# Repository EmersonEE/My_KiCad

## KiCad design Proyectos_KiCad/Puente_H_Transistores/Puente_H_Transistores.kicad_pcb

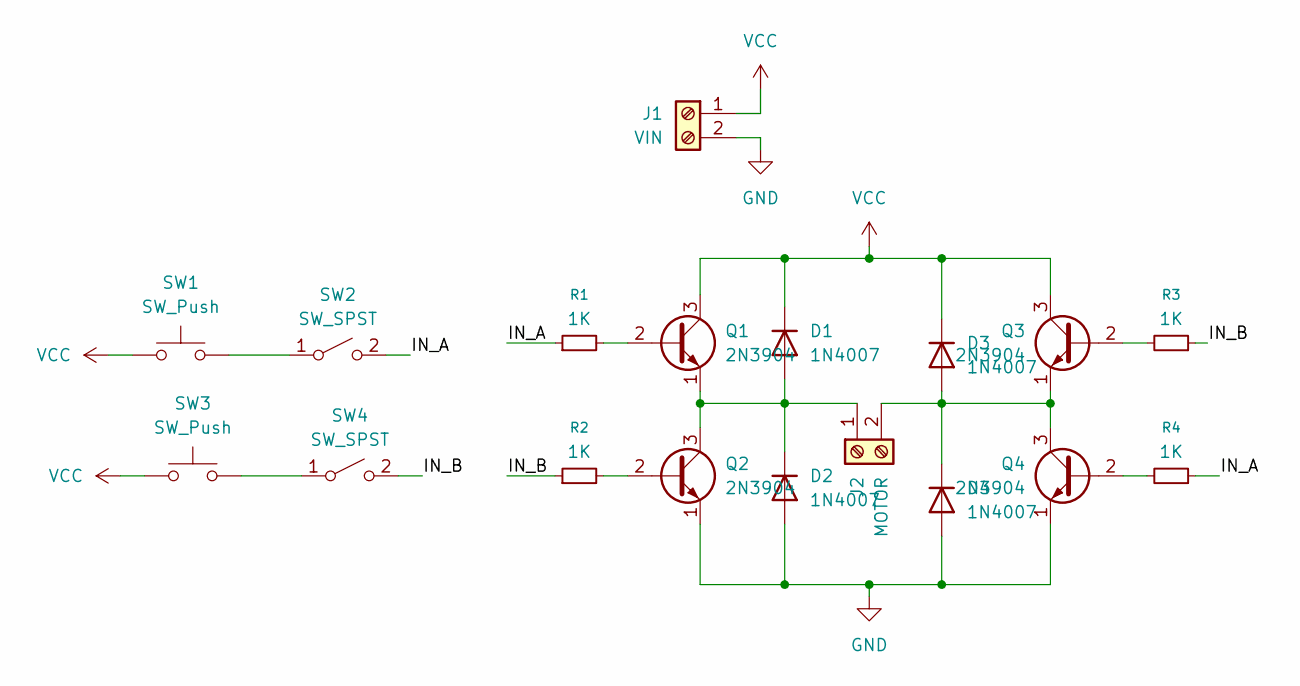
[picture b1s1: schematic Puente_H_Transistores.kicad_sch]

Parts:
D1, D2, D3, D4: 1N4007; D_DO-41_SOD81_P10.16mm_Horizontal
J1: VIN; TerminalBlock_Phoenix_MKDS-1,5-2-5.08_1x02_P5.08mm_Horizont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
J2: MOTOR; TerminalBlock_Phoenix_MKDS-1,5-2-5.08_1x02_P5.08mm_Horizont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
Q1, Q2, Q3, Q4: 2N3904; TO-92L_Inline_Wide
R1, R2, R3, R4: 1K; R_Axial_DIN0207_L6.3mm_D2.5mm_P10.16mm_Horizontal
SW1, SW3: SW_Push; TerminalBlock_Phoenix_MKDS-1,5-2-5.08_1x02_P5.08mm_Horizont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
SW2, SW4: SW_SPST; TerminalBlock_Phoenix_MKDS-1,5-2-5.08_1x02_P5.08mm_Horizont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

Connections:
/IN_A: R1.1, R4.1, SW2.2 (B)
/IN_B: R2.1, R3.1, SW4.2 (B)
GND: D2.2 (A), D4.2 (A), J1.2, Q2.1 (E), Q4.1 (E)
unnamed: D1.2 (A), D2.1 (K), J2.1, Q1.1 (E), Q2.3 (C)
unnamed: D3.2 (A), D4.1 (K), J2.2, Q3.1 (E), Q4.3 (C)
unnamed: Q1.2 (B), R1.2
unnamed: Q2.2 (B), R2.2
unnamed: Q3.2 (B), R3.2
unnamed: Q4.2 (B), R4.2
unnamed: SW1.2, SW2.1 (A)
unnamed: SW3.2, SW4.1 (A)
VCC: D1.1 (K), D3.1 (K), J1.1, Q1.3 (C), Q3.3 (C), SW1.1, SW3.1

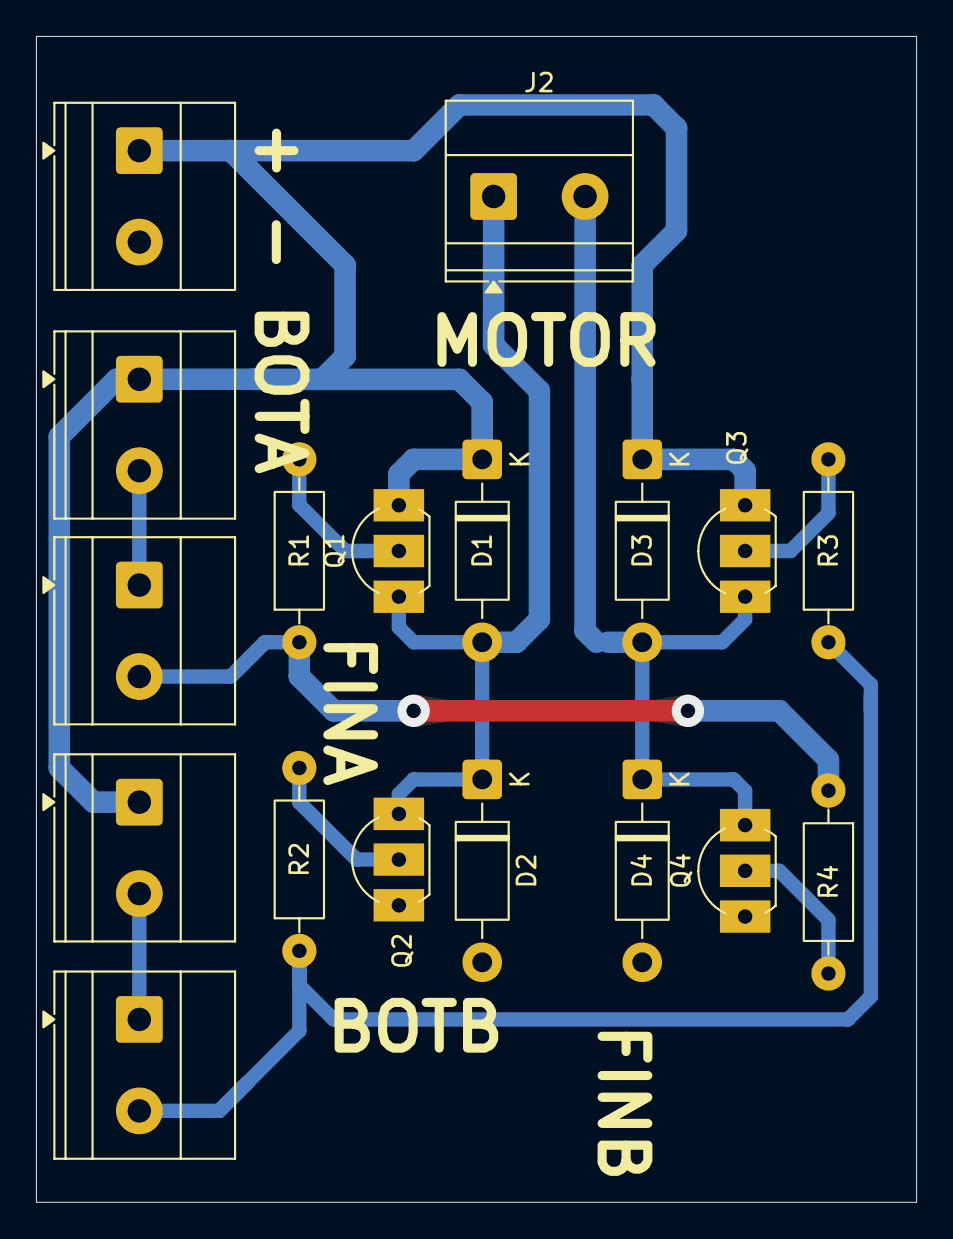
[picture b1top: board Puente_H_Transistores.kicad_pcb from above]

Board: 2 copper layers, 48.9 x 64.8 mm, 18 parts (0 on the bottom side), 12 nets.

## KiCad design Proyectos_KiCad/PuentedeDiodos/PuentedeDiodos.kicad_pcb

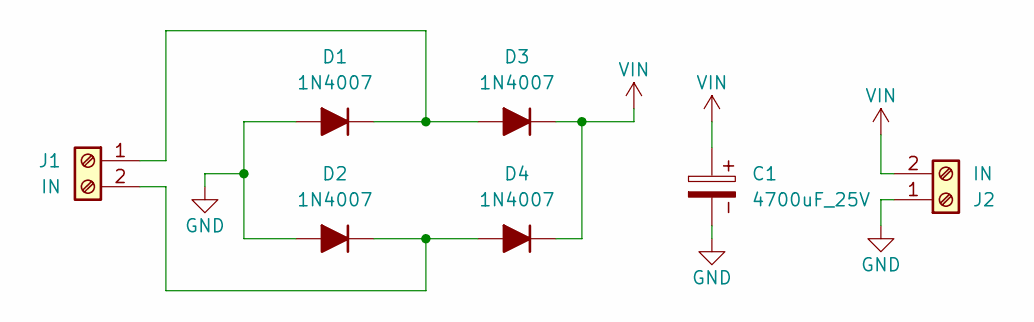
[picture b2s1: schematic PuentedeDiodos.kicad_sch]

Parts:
C1: 4700uF_25V; CP_Radial_D18.0mm_P7.50mm
D1, D2, D3, D4: 1N4007; D_DO-41_SOD81_P7.62mm_Horizontal
J1, J2: IN; TerminalBlock_Phoenix_MKDS-1,5-2-5.08_1x02_P5.08mm_Horizont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

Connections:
GND: C1.2, D1.2 (A), D2.2 (A), J2.1
unnamed: D1.1 (K), D3.2 (A), J1.1
unnamed: D2.1 (K), D4.2 (A), J1.2
VIN: C1.1, D3.1 (K), D4.1 (K), J2.2

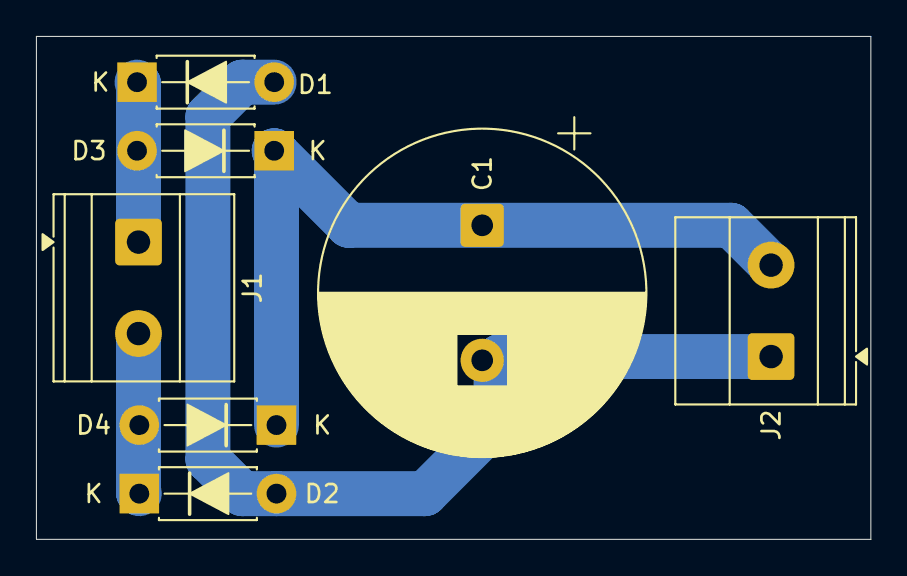
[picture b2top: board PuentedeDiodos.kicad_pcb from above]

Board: 2 copper layers, 46.4 x 27.9 mm, 7 parts (0 on the bottom side), 4 nets.

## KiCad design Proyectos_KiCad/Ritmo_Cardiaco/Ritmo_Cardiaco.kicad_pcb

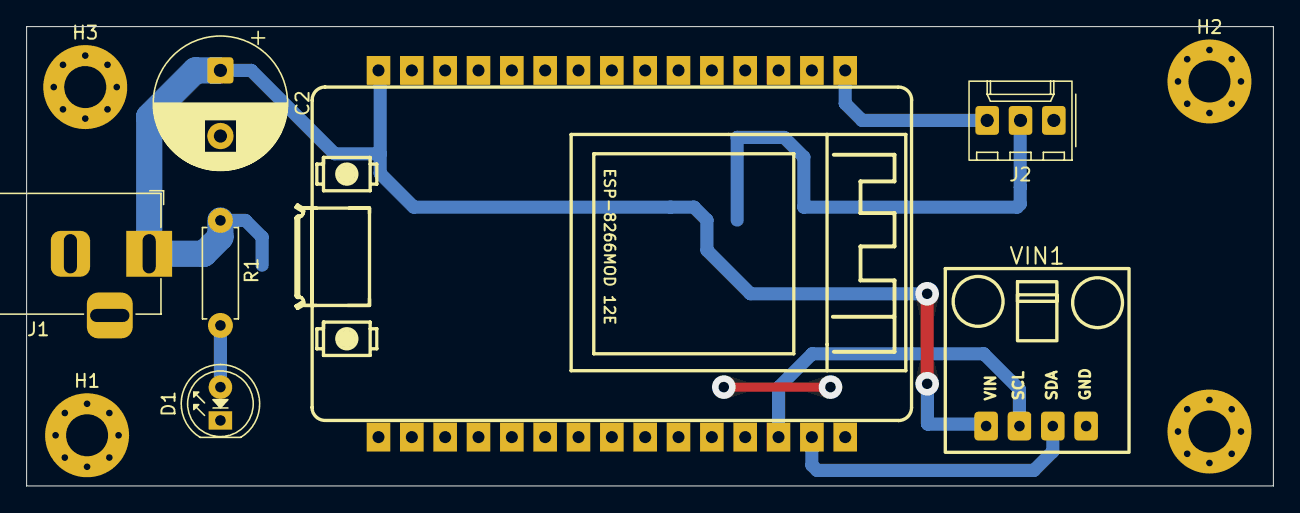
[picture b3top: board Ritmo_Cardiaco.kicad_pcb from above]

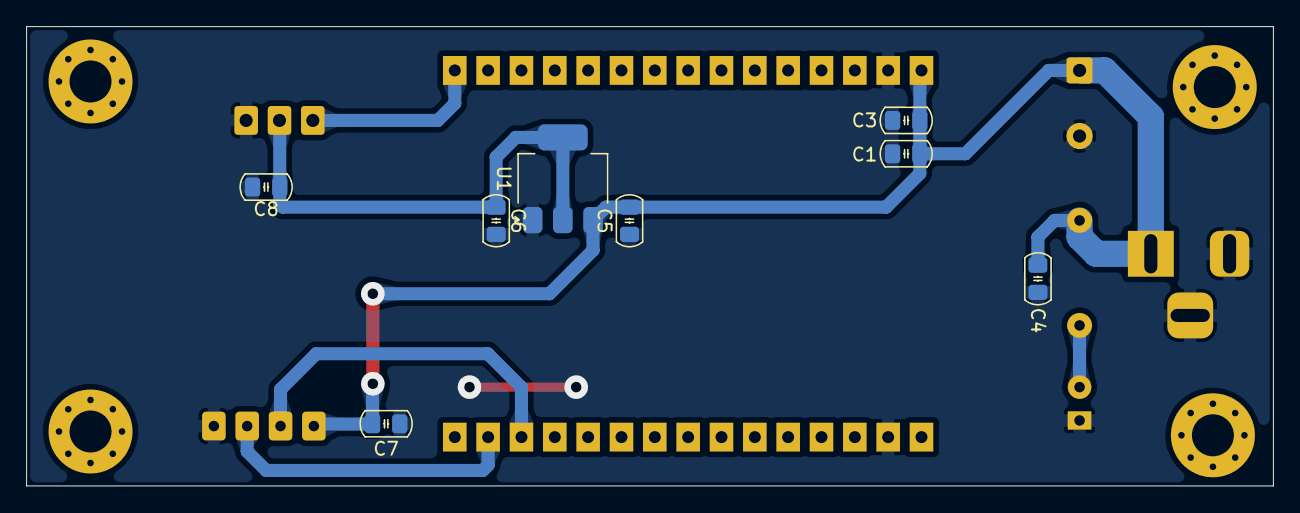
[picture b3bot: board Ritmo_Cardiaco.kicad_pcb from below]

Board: 2 copper layers, 95.0 x 35.0 mm, 19 parts (8 on the bottom side), 7 nets.

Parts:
C1, C3, C4, C7, C8: 100nF; C_0805_2012Metric_Pad1.18x1.45mm
C2: 250uF/15V; CP_Radial_D10.0mm_P5.00mm
C5, C6: 10uF/16V; C_0805_2012Metric_Pad1.18x1.45mm
D1: RED; LED_D5.0mm
H1, H2, H3, H4: MountingHole_3.2mm_M3_Pad_Via
J1: Barrel_Jack_Switch; BarrelJack_Horizontal
J2: SENSOR; Molex_KK-254_AE-6410-03A_1x03_P2.54mm_Vertical
NODE1: MCU-ESP8266; NODEMCU-12E_Grande
R1: 2K
U1: AMS1117-3.3; SOT-223-3_TabPin2
VIN1: MAX30102; MAX30102-MODULE-FOOTPRINT

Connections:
+3.3V: C6.1, C8.1, J2.2, U1.2 (VO)
+5V: C1.1, C2.1, C3.1, C4.1, C5.1, C7.1, J1.1, NODE1.29 (Vin), R1.1, U1.3 (VI), VIN1.1 (VIN)
GND: C1.2, C2.2, C3.2, C4.2, C5.2, C6.2, C7.2, C8.2, D1.1 (K), J1.2, J1.3, J2.1, NODE1.13 (GND), NODE1.28 (GND), U1.1 (GND), VIN1.4 (GND)
unnamed: D1.2 (A), R1.2
SCL: NODE1.2 (D2), VIN1.2 (SCL)
SDA: NODE1.1 (D1), VIN1.3 (SDA)
SEN: J2.3, NODE1.15 (A0)

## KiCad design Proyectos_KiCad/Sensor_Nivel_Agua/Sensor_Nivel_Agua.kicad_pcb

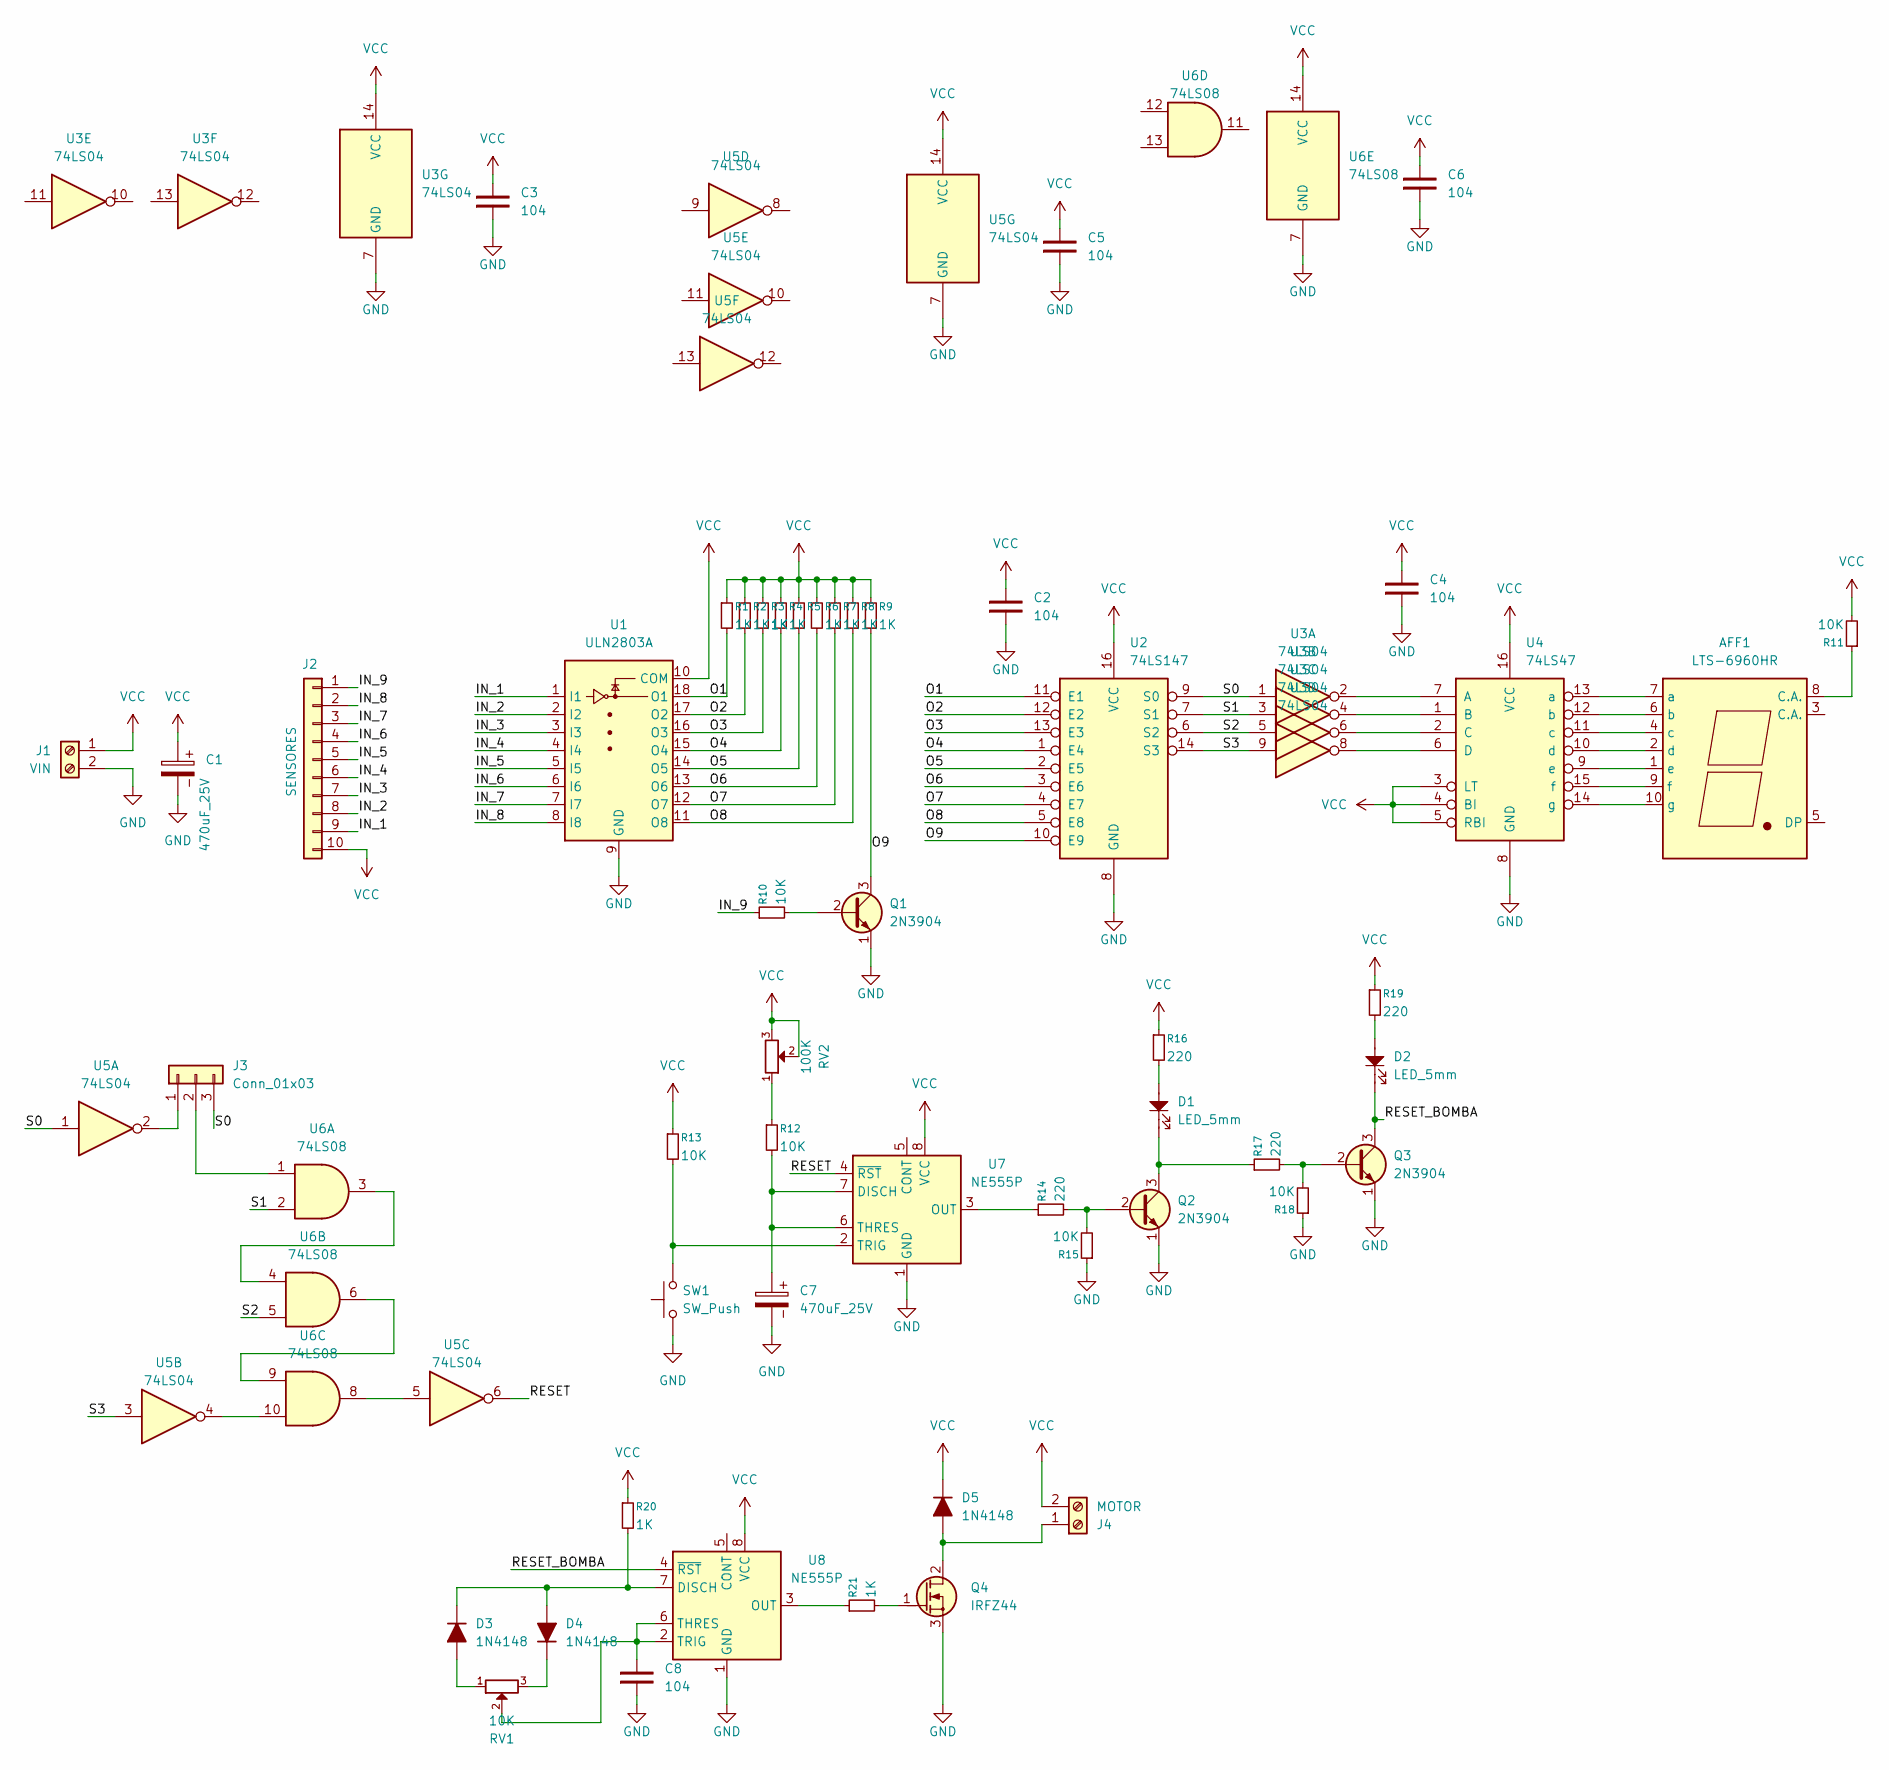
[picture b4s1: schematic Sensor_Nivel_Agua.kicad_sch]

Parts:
AFF1: LTS-6960HR; 7SegmentLED_LTS6760_LTS6780
C1, C7: 470uF_25V; CP_Radial_D8.0mm_P3.50mm
C2, C3, C4, C5, C6, C8: 104; C_Disc_D5.0mm_W2.5mm_P2.50mm
D1, D2: LED_5mm; LED_D5.0mm_Clear
D3, D4, D5: 1N4148; D_DO-35_SOD27_P7.62mm_Horizontal
J1: VIN; TerminalBlock_Phoenix_MKDS-1,5-2-5.08_1x02_P5.08mm_Horizont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
J2: SENSORES; PinHeader_1x10_P2.54mm_Vertical
J3: Conn_01x03; PinHeader_1x03_P2.54mm_Vertical
J4: MOTOR; TerminalBlock_Phoenix_MKDS-1,5-2-5.08_1x02_P5.08mm_Horizont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
Q1, Q2, Q3: 2N3904; TO-92_Inline_Wide_EBC
Q4: IRFZ44; TO-220-3_Vertical_GDS
R1, R2, R3, R4, R5, R6, R7, R8, R9: 1K; R_Axial_DIN0207_L6.3mm_D2.5mm_P15.24mm_Horizontal
R10, R11, R12, R13, R15, R18: 10K; R_Axial_DIN0207_L6.3mm_D2.5mm_P10.16mm_Horizontal
R14, R16, R17, R19: 220; R_Axial_DIN0207_L6.3mm_D2.5mm_P10.16mm_Horizontal
R20, R21: 1K; R_Axial_DIN0207_L6.3mm_D2.5mm_P10.16mm_Horizontal
RV1: 10K; Potentiometer_Alps_RK163_Single_Horizontal
RV2: 100K; Potentiometer_Bourns_3296W_Vertical
SW1: SW_Push; Push_PTH_12x12mm
U1: ULN2803A; DIP-18_W7.62mm_LongPads
U2: 74LS147; DIP-16_W7.62mm_LongPads
U3, U5: 74LS04; DIP-14_W7.62mm_LongPads
U4: 74LS47; DIP-16_W7.62mm_LongPads
U6: 74LS08; DIP-14_W7.62mm_LongPads
U7, U8: NE555P; DIP-8_W7.62mm_LongPads

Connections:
/IN_1: J2.9, U1.1 (I1)
/IN_2: J2.8, U1.2 (I2)
/IN_3: J2.7, U1.3 (I3)
/IN_4: J2.6, U1.4 (I4)
/IN_5: J2.5, U1.5 (I5)
/IN_6: J2.4, U1.6 (I6)
/IN_7: J2.3, U1.7 (I7)
/IN_8: J2.2, U1.8 (I8)
/IN_9: J2.1, R10.1
/O1: R1.2, U1.18 (O1), U2.11 (E1)
/O2: R2.2, U1.17 (O2), U2.12 (E2)
/O3: R3.2, U1.16 (O3), U2.13 (E3)
/O4: R4.2, U1.15 (O4), U2.1 (E4)
/O5: R5.2, U1.14 (O5), U2.2 (E5)
/O6: R6.2, U1.13 (O6), U2.3 (E6)
/O7: R7.2, U1.12 (O7), U2.4 (E7)
/O8: R8.2, U1.11 (O8), U2.5 (E8)
/O9: Q1.3 (C), R9.2, U2.10 (E9)
/RESET: U5.6, U7.4 (~RST)
/RESET_BOMBA: D2.1, Q3.3 (C), U8.4 (~RST)
/S0: J3.3, U2.9 (S0), U3.1, U5.1
/S1: U2.7 (S1), U3.3, U6.2
/S2: U2.6 (S2), U3.5, U6.5
/S3: U2.14 (S3), U3.9, U5.3
GND: C1.2, C2.1, C3.1, C4.1, C5.1, C6.1, C7.2, C8.1, J1.2, Q1.1 (E), Q2.1 (E), Q3.1 (E), Q4.3 (S), R15.1, R18.1, SW1.1, U1.9 (GND), U2.8 (GND), U3.7 (GND), U4.8 (GND), U5.7 (GND), U6.7 (GND), U7.1 (GND), U8.1 (GND)
unnamed: AFF1.8 (C.A.), R11.1
unnamed: AFF1.7 (a), U4.13 (a)
unnamed: AFF1.6 (b), U4.12 (b)
unnamed: AFF1.4 (c), U4.11 (c)
unnamed: AFF1.2 (d), U4.10 (d)
unnamed: AFF1.1 (e), U4.9 (e)
unnamed: AFF1.9 (f), U4.15 (f)
unnamed: AFF1.10 (g), U4.14 (g)
unnamed: D1.2, R16.2
unnamed: D2.2, R19.2
unnamed: D3.2 (A), RV1.1
unnamed: D3.1 (K), D4.2 (A), R20.2, U8.7 (DISCH)
unnamed: D4.1 (K), RV1.3
unnamed: D5.2 (A), J4.1, Q4.2 (D)
unnamed: J3.1, U5.2
unnamed: J3.2, U6.1
unnamed: Q1.2 (B), R10.2
unnamed: Q2.2 (B), R14.2, R15.2
unnamed: D1.1, Q2.3 (C), R17.1
unnamed: Q3.2 (B), R17.2, R18.2
unnamed: Q4.1 (G), R21.2
unnamed: R12.1, RV2.1
unnamed: U3.2, U4.7 (A)
unnamed: U3.4, U4.1 (B)
unnamed: U3.6, U4.2 (C)
unnamed: U3.8, U4.6 (D)
unnamed: U5.4, U6.10
unnamed: U5.5, U6.8
unnamed: U6.3, U6.4
unnamed: U6.6, U6.9
unnamed: C7.1, R12.2, U7.6 (THRES), U7.7 (DISCH)
unnamed: R14.1, U7.3 (OUT)
unnamed: R13.2, SW1.2, U7.2 (TRIG)
unnamed: R21.1, U8.3 (OUT)
unnamed: C8.2, RV1.2, U8.2 (TRIG), U8.6 (THRES)
VCC: C1.1, C2.2, C3.2, C4.2, C5.2, C6.2, D5.1 (K), J1.1, J2.10, J4.2, R1.1, R2.1, R3.1, R4.1, R5.1, R6.1, R7.1, R8.1, R9.1, R11.2, R13.1, R16.1, R19.1, R20.1, RV2.2, RV2.3, U1.10 (COM), U2.16 (VCC), U3.14 (VCC), U4.3 (LT), U4.4 (BI), U4.5 (RBI), U4.16 (VCC), U5.14 (VCC), U6.14 (VCC), U7.8 (VCC), U8.8 (VCC)

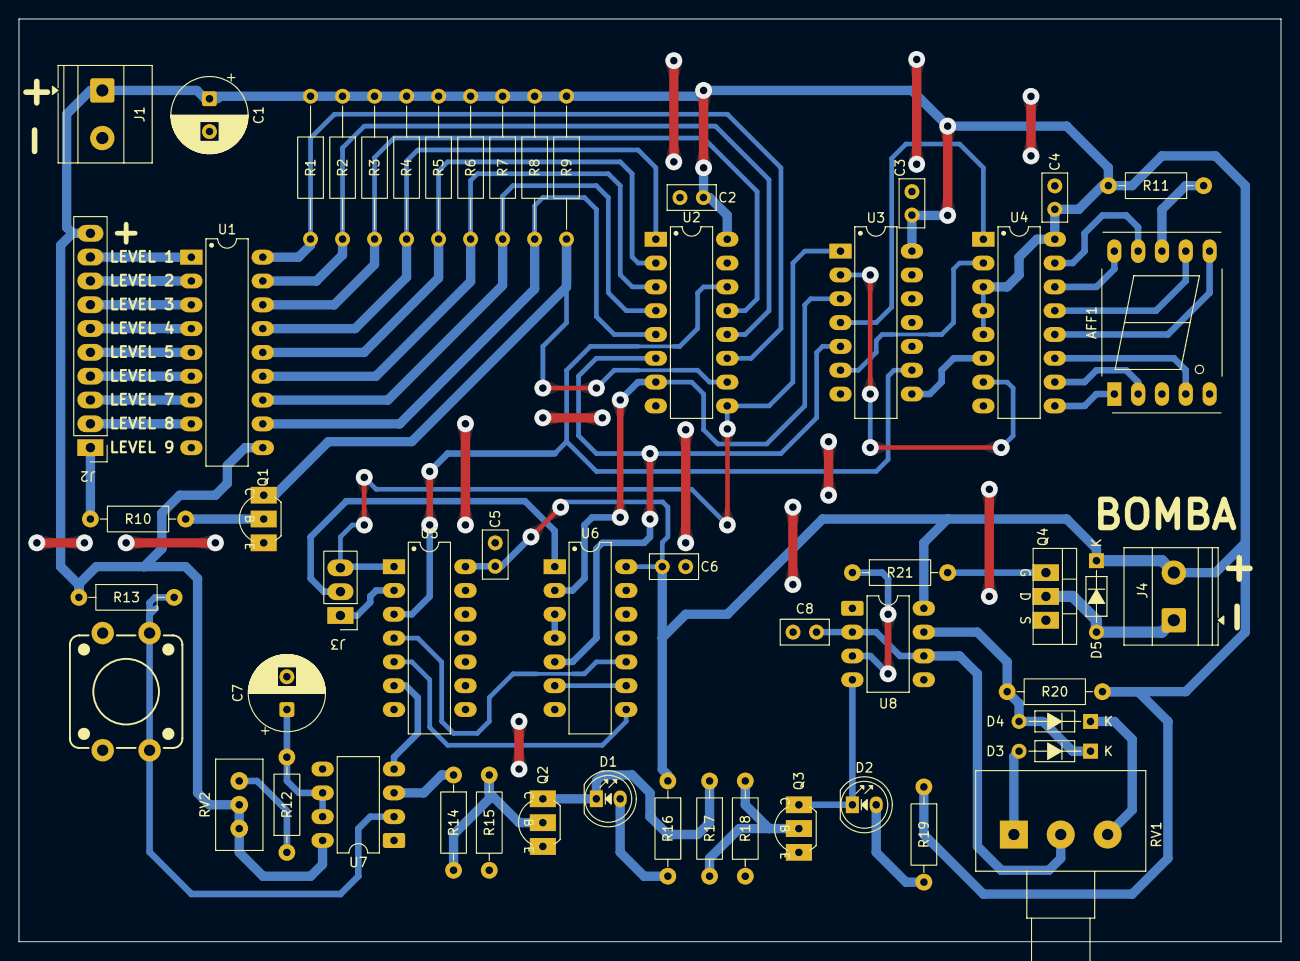
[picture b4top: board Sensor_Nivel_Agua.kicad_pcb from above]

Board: 2 copper layers, 134.6 x 98.4 mm, 54 parts (0 on the bottom side), 61 nets.

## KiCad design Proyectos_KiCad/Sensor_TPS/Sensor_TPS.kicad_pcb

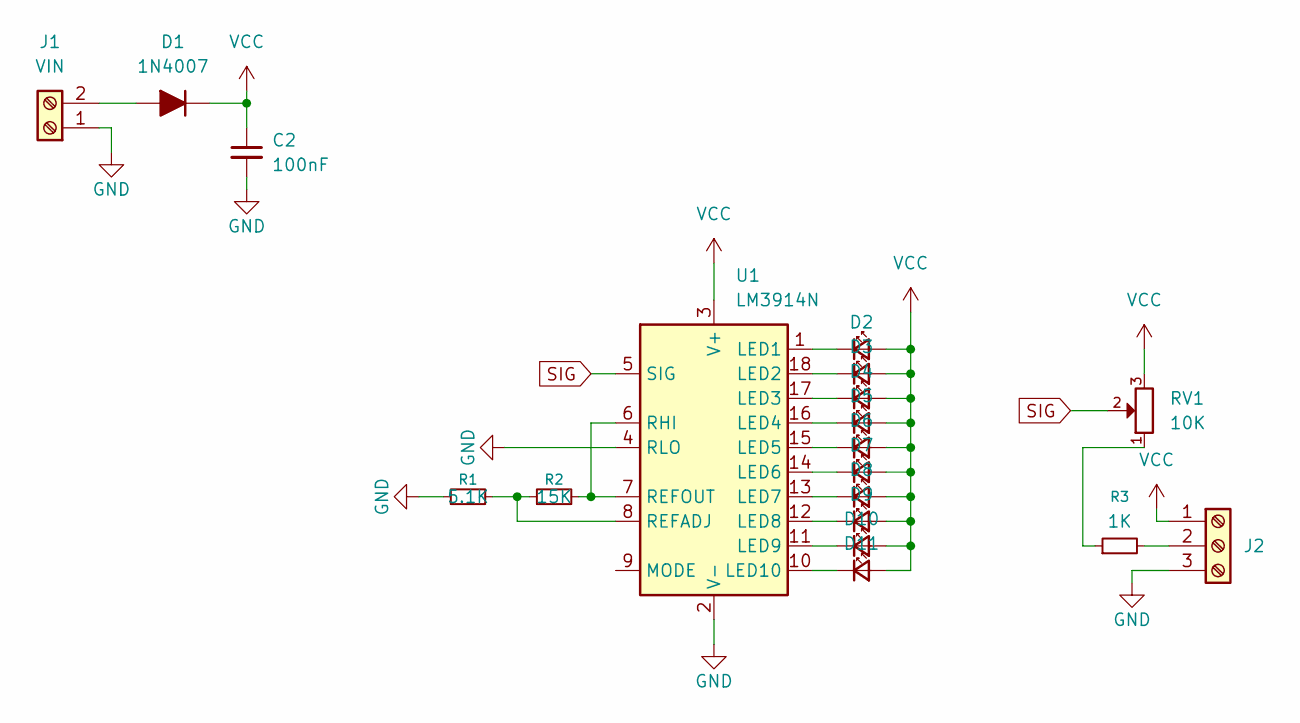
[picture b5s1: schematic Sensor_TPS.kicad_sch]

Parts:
C2: 100nF; C_Disc_D3.8mm_W2.6mm_P2.50mm
D1: 1N4007; D_DO-41_SOD81_P7.62mm_Horizontal
D2, D3, D4, D5, D6, D7, D8, D9, D10, D11: LED_Small; LED_D5.0mm
J1: VIN; TerminalBlock_Phoenix_MKDS-1,5-2-5.08_1x02_P5.08mm_Horizont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
J2: Screw_Terminal_01x03; TerminalBlock_Phoenix_MKDS-1,5-3-5.08_1x03_P5.08mm_Horizont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
R1: 5.1K; 1K
R2: 15K; 1K
R3: 1K
RV1: 10K; Potentiometer_Alps_RK163_Single_Horizontal
U1: LM3914N; DIP-18_W7.62mm_LongPads

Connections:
GND: C2.2, J1.1, J2.3, R1.1, U1.2 (V-), U1.4 (RLO)
unnamed: D1.2 (A), J1.2
unnamed: D2.1 (K), U1.1 (LED1)
unnamed: D3.1 (K), U1.18 (LED2)
unnamed: D4.1 (K), U1.17 (LED3)
unnamed: D5.1 (K), U1.16 (LED4)
unnamed: D6.1 (K), U1.15 (LED5)
unnamed: D7.1 (K), U1.14 (LED6)
unnamed: D8.1 (K), U1.13 (LED7)
unnamed: D9.1 (K), U1.12 (LED8)
unnamed: D10.1 (K), U1.11 (LED9)
unnamed: D11.1 (K), U1.10 (LED10)
unnamed: J2.2, R3.2
unnamed: R3.1, RV1.1
unnamed: R1.2, R2.1, U1.8 (REFADJ)
unnamed: R2.2, U1.6 (RHI), U1.7 (REFOUT)
SIG: RV1.2, U1.5 (SIG)
VCC: C2.1, D1.1 (K), D2.2 (A), D3.2 (A), D4.2 (A), D5.2 (A), D6.2 (A), D7.2 (A), D8.2 (A), D9.2 (A), D10.2 (A), D11.2 (A), J2.1, RV1.3, U1.3 (V+)

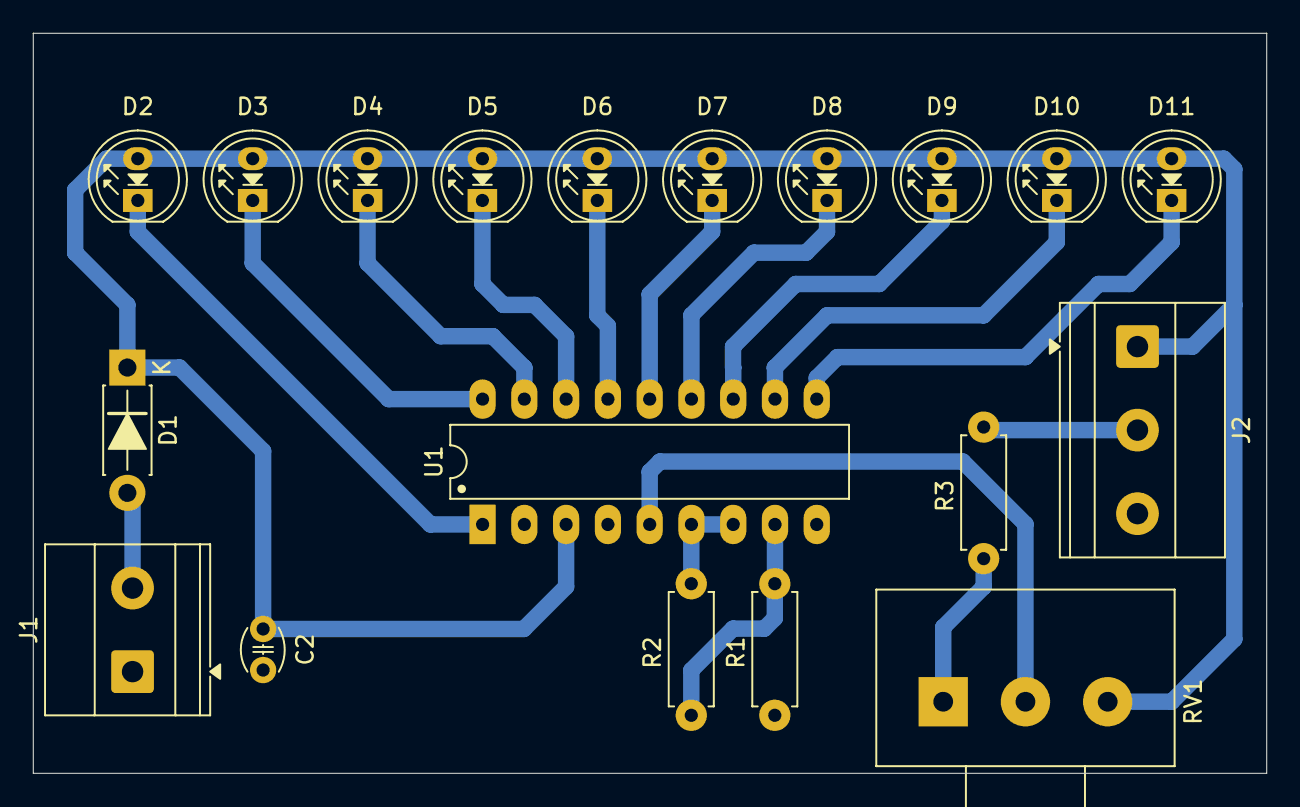
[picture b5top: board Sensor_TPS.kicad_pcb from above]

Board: 2 copper layers, 75.0 x 45.0 mm, 19 parts (0 on the bottom side), 18 nets.

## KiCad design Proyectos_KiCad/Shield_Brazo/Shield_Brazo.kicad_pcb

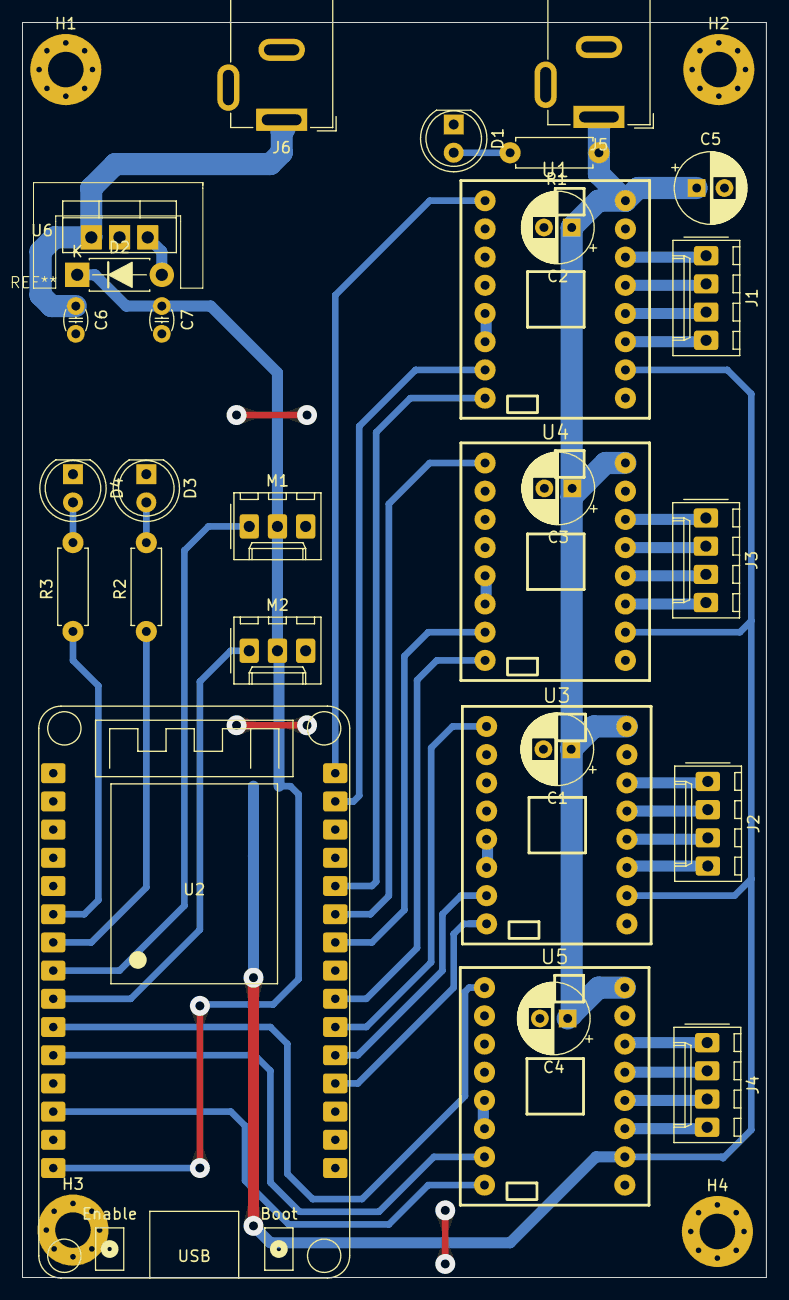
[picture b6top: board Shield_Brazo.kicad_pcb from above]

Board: 2 copper layers, 67.0 x 113.0 mm, 33 parts (1 on the bottom side), 45 nets.

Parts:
C1, C2, C3, C4, C5: 100uF/25V; CP_Radial_D6.3mm_P2.50mm
C6, C7: 100nF; C_Disc_D3.4mm_W2.1mm_P2.50mm
D1, D3, D4: LED_D5.0mm
D2: 1N4007; D_DO-41_SOD81_P7.62mm_Horizontal
H1, H2, H3, H4: MountingHole_3.2mm_M3_Pad_Via
J1, J2, J3, J4: MOTOR; Molex_KK-254_AE-6410-04A_1x04_P2.54mm_Vertical
J5, J6: INPUT; BarrelJack_GCT_DCJ200-10-A_Horizontal
M1, M2: Molex_KK-254_AE-6410-03A_1x03_P2.54mm_Vertical
R1, R2, R3: 1K
U1, U3, U4, U5: TMC2209; D_TMC2209_Ca
U2: ESP32_DevKit_V1_DOIT; ESP32_DEVKIT_V1_E32
U6: LM7805CT; TO-220-3_Vertical
U7: AMS1117-3.3; SOT-223-3_TabPin2

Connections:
+3.3V: U1.10 (VDD), U3.10 (VDD), U4.10 (VDD), U5.10 (VDD), U7.2 (VO)
+5V: C7.1, D2.1 (K), M1.2 (+), M2.2 (+), U2.15 (VIN), U7.3 (VI)
+12V: C1.1, C2.1, C3.1, C4.1, C5.1, J5.1, R1.1, U1.16 (VMOT), U3.16 (VMOT), U4.16 (VMOT), U5.16 (VMOT)
DIR_M1: U1.8 (DIR), U2.26 (SDA/GPIO21/D21)
DIR_M2: U2.22 (UART2TX/GPIO17/D17), U4.8 (DIR)
DIR_M3: U2.19 (TOUCH2/ADC2/GPIO2/D2), U3.8 (DIR)
DIR_M4: U2.13 (D13/GPIO13/ADC2/TOUCH4), U5.8 (DIR)
EN_M1: U1.1 (EN), U2.30 (MOSI/GPIO23/D23)
EN_M2: U2.25 (MISO/GPIO19/D19), U4.1 (EN)
EN_M3: U2.21 (UART2RX/GPIO16/D16), U3.1 (EN)
EN_M4: U2.10 (D27/GPIO27/ADC2/TOUCH7), U5.1 (EN)
GND: C1.2, C2.2, C3.2, C4.2, C5.2, C6.2, C7.2, D1.1 (K), D3.1 (K), D4.1 (K), J5.2, J5.3, J6.2, J6.3, M1.3 (-), M2.3 (-), U1.9 (GND), U1.15 (GND), U2.14 (GND), U2.17 (GND), U3.9 (GND), U3.15 (GND), U4.9 (GND), U4.15 (GND), U5.9 (GND), U5.15 (GND), U6.2, U7.1 (GND)
LED1: R2.1, U2.7 (D33/GPIO33/ADC1/TOUCH8)
LED2: R3.1, U2.6 (D32/GPIO32/ADC1/TOUCH9)
unnamed: D1.2 (A), R1.2
unnamed: D2.2 (A), U6.3 (OUT)
unnamed: D3.2 (A), R2.2
unnamed: D4.2 (A), R3.2
unnamed: J1.1, U1.14 (B2)
unnamed: J1.2, U1.13 (A2)
unnamed: J1.3, U1.12 (A1)
unnamed: J1.4, U1.11 (B1)
unnamed: J2.1, U3.14 (B2)
unnamed: J2.2, U3.13 (A2)
unnamed: J2.3, U3.12 (A1)
unnamed: J2.4, U3.11 (B1)
unnamed: J3.1, U4.14 (B2)
unnamed: J3.2, U4.13 (A2)
unnamed: J3.3, U4.12 (A1)
unnamed: J3.4, U4.11 (B1)
unnamed: J4.1, U5.14 (B2)
unnamed: J4.2, U5.13 (A2)
unnamed: J4.3, U5.12 (A1)
unnamed: J4.4, U5.11 (B1)
unnamed: U1.5 (RESET/USART), U1.6 (SLEEP/CLK)
unnamed: U3.5 (RESET/USART), U3.6 (SLEEP/CLK)
unnamed: U4.5 (RESET/USART), U4.6 (SLEEP/CLK)
unnamed: U5.5 (RESET/USART), U5.6 (SLEEP/CLK)
unnamed: C6.1, J6.1, U6.1 (IN)
SERVO_1: M1.1 (PWM), U2.8 (D25/GPIO25/ADC2/DAC1)
SERVO_2: M2.1 (PWM), U2.9 (D26/GPIO26/ADC2/DAC2)
STEP_M1: U1.7 (STEP), U2.29 (SCL/GPIO22/D22)
STEP_M2: U2.24 (CLK/GPIO18/D18), U4.7 (STEP)
STEP_M3: U2.20 (TOUCH0/ADC2/GPIO4/D4), U3.7 (STEP)
STEP_M4: U2.11 (D14/GPIO14/ADC2/TOUCH6), U5.7 (STEP)

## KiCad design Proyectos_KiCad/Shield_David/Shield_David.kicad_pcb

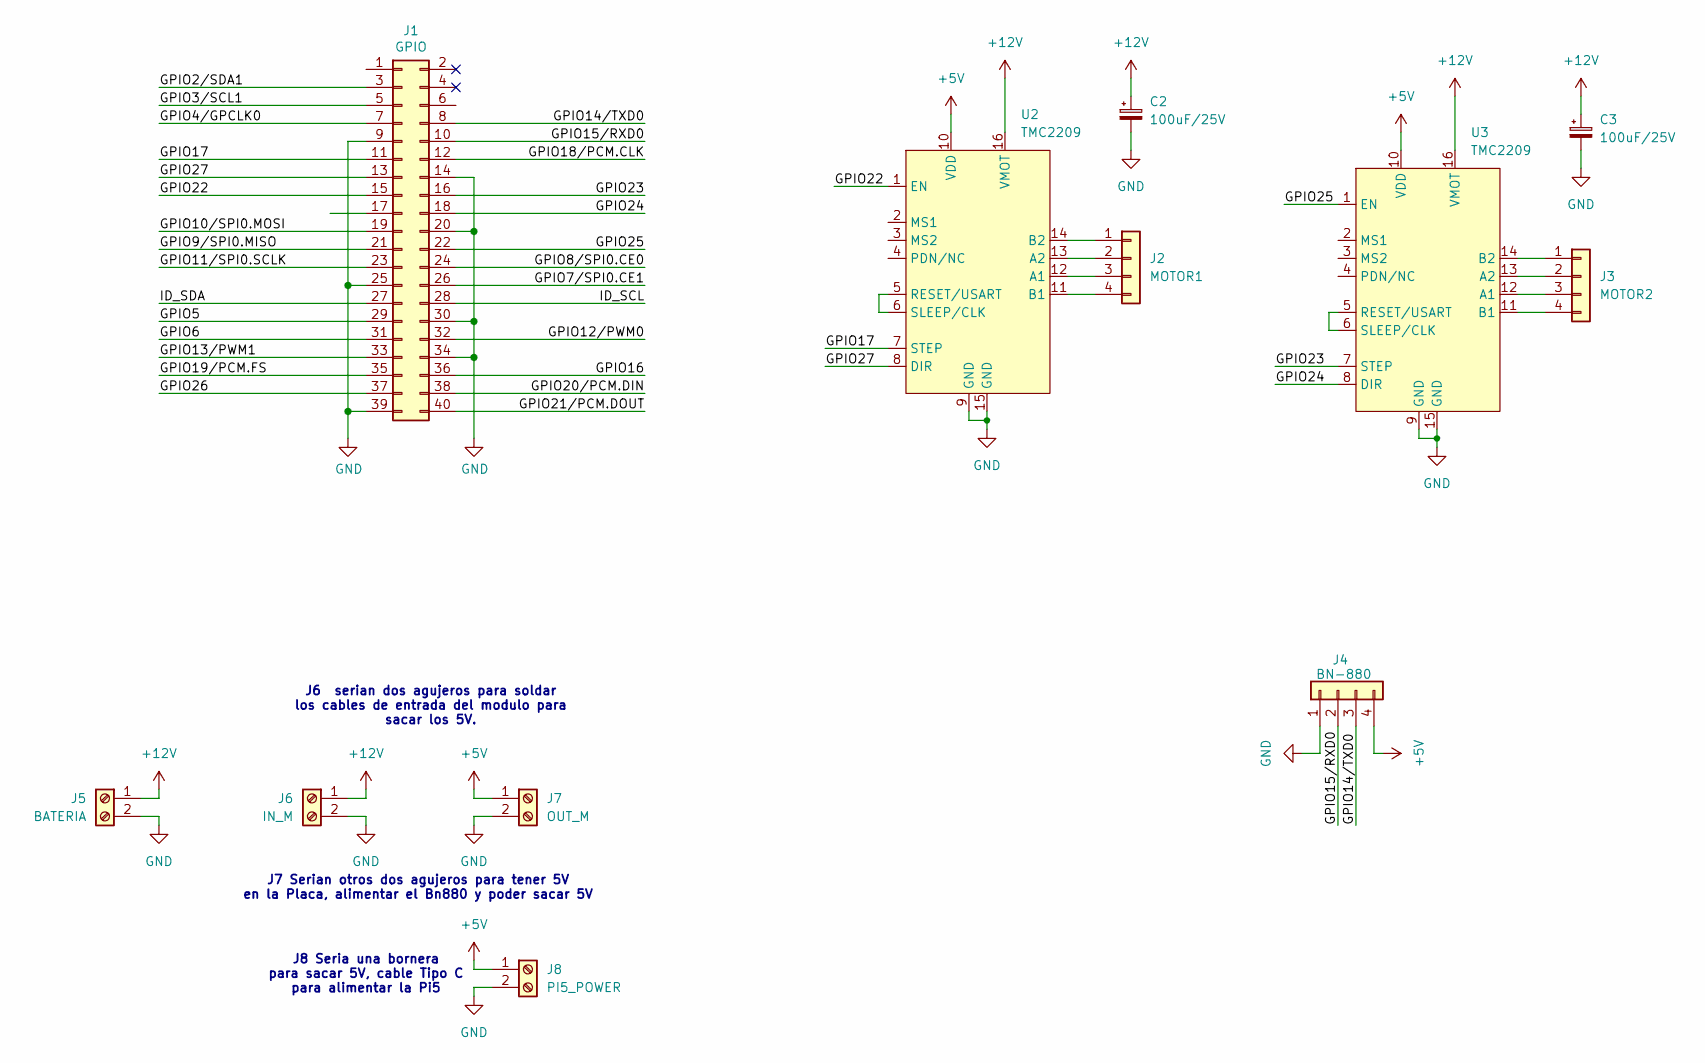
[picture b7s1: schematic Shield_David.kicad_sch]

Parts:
C2, C3: 100uF/25V; CP_Radial_D8.0mm_P3.50mm
J1: GPIO; PinHeader_2x20_P2.54mm_Horizontal
J2: MOTOR1; TerminalBlock_Phoenix_MKDS-1,5-4-5.08_1x04_P5.08mm_Horizont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
J3: MOTOR2; TerminalBlock_Phoenix_MKDS-1,5-4-5.08_1x04_P5.08mm_Horizont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
J4: BN-880; Molex_KK-254_AE-6410-04A_1x04_P2.54mm_Vertical
J5: BATERIA; TerminalBlock_Phoenix_MKDS-1,5-2-5.08_1x02_P5.08mm_Horizont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
J6: IN_M; TerminalBlock_Phoenix_MKDS-1,5-2-5.08_1x02_P5.08mm_Horizont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
J7: OUT_M; TerminalBlock_Phoenix_MKDS-1,5-2-5.08_1x02_P5.08mm_Horizont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
J8: PI5_POWER; TerminalBlock_Phoenix_MKDS-1,5-2-5.08_1x02_P5.08mm_Horizont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
U2, U3: TMC2209

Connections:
+5V: J4.4, J7.1, J8.1, U2.10 (VDD), U3.10 (VDD)
+12V: C2.1, C3.1, J5.1, J6.1, U2.16 (VMOT), U3.16 (VMOT)
/GPIO2/SDA1: J1.3
/GPIO3/SCL1: J1.5
/GPIO4/GPCLK0: J1.7
/GPIO5: J1.29
/GPIO6: J1.31
/GPIO7/SPI0.CE1: J1.26
/GPIO8/SPI0.CE0: J1.24
/GPIO9/SPI0.MISO: J1.21
/GPIO10/SPI0.MOSI: J1.19
/GPIO11/SPI0.SCLK: J1.23
/GPIO12/PWM0: J1.32
/GPIO13/PWM1: J1.33
/GPIO14/TXD0: J1.8, J4.3
/GPIO15/RXD0: J1.10, J4.2
/GPIO16: J1.36
/GPIO17: J1.11, U2.7 (STEP)
/GPIO18/PCM.CLK: J1.12
/GPIO19/PCM.FS: J1.35
/GPIO20/PCM.DIN: J1.38
/GPIO21/PCM.DOUT: J1.40
/GPIO22: J1.15, U2.1 (EN)
/GPIO23: J1.16, U3.7 (STEP)
/GPIO24: J1.18, U3.8 (DIR)
/GPIO25: J1.22, U3.1 (EN)
/GPIO26: J1.37
/GPIO27: J1.13, U2.8 (DIR)
/ID_SCL: J1.28
/ID_SDA: J1.27
GND: C2.2, C3.2, J1.9, J1.14, J1.20, J1.25, J1.30, J1.34, J1.39, J4.1, J5.2, J6.2, J7.2, J8.2, U2.9 (GND), U2.15 (GND), U3.9 (GND), U3.15 (GND)
unnamed: J2.1, U2.14 (B2)
unnamed: J2.2, U2.13 (A2)
unnamed: J2.3, U2.12 (A1)
unnamed: J2.4, U2.11 (B1)
unnamed: J3.1, U3.14 (B2)
unnamed: J3.2, U3.13 (A2)
unnamed: J3.3, U3.12 (A1)
unnamed: J3.4, U3.11 (B1)
unnamed: U2.5 (RESET/USART), U2.6 (SLEEP/CLK)
unnamed: U3.5 (RESET/USART), U3.6 (SLEEP/CLK)

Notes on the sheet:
J6 serian dos agujeros para soldar los cables de entrada del modulo para sacar los 5V.
J8 Seria una bornera para sacar 5V, cable Tipo C para alimentar la Pi5
J7 Serian otros dos agujeros para tener 5V en la Placa, alimentar el Bn880 y poder sacar 5V

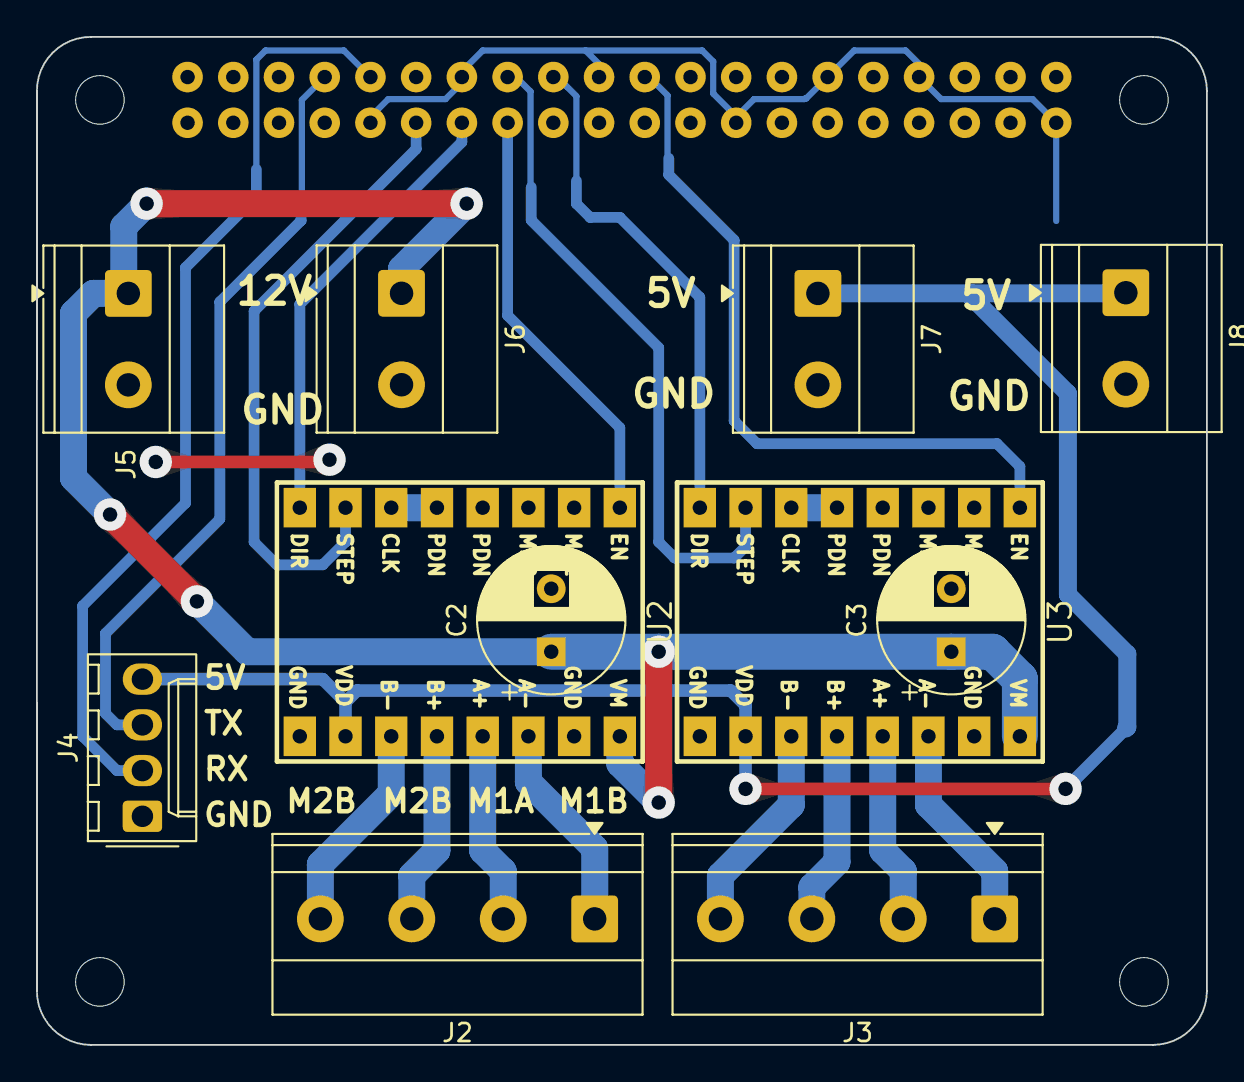
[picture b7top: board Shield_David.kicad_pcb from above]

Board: 2 copper layers, 65.0 x 56.0 mm, 16 parts (1 on the bottom side), 21 nets.

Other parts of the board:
MH1, MH2, MH3, MH4: MountingHole_2.7mm_M2.5
